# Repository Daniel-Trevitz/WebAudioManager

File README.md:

# WebAudioManager
Server program for single instance audio control via web interface

This program provides a web interface for controling an audio card.
KiCad design is found in EE folder.

This is meant to be a very simple interface with as few knobs to turn as possible

The interface is designed for mobile devices, but is functional on desktops.

http server provided by https://github.com/etr/libhttpserver
json server provided by https://github.com/nlohmann/json

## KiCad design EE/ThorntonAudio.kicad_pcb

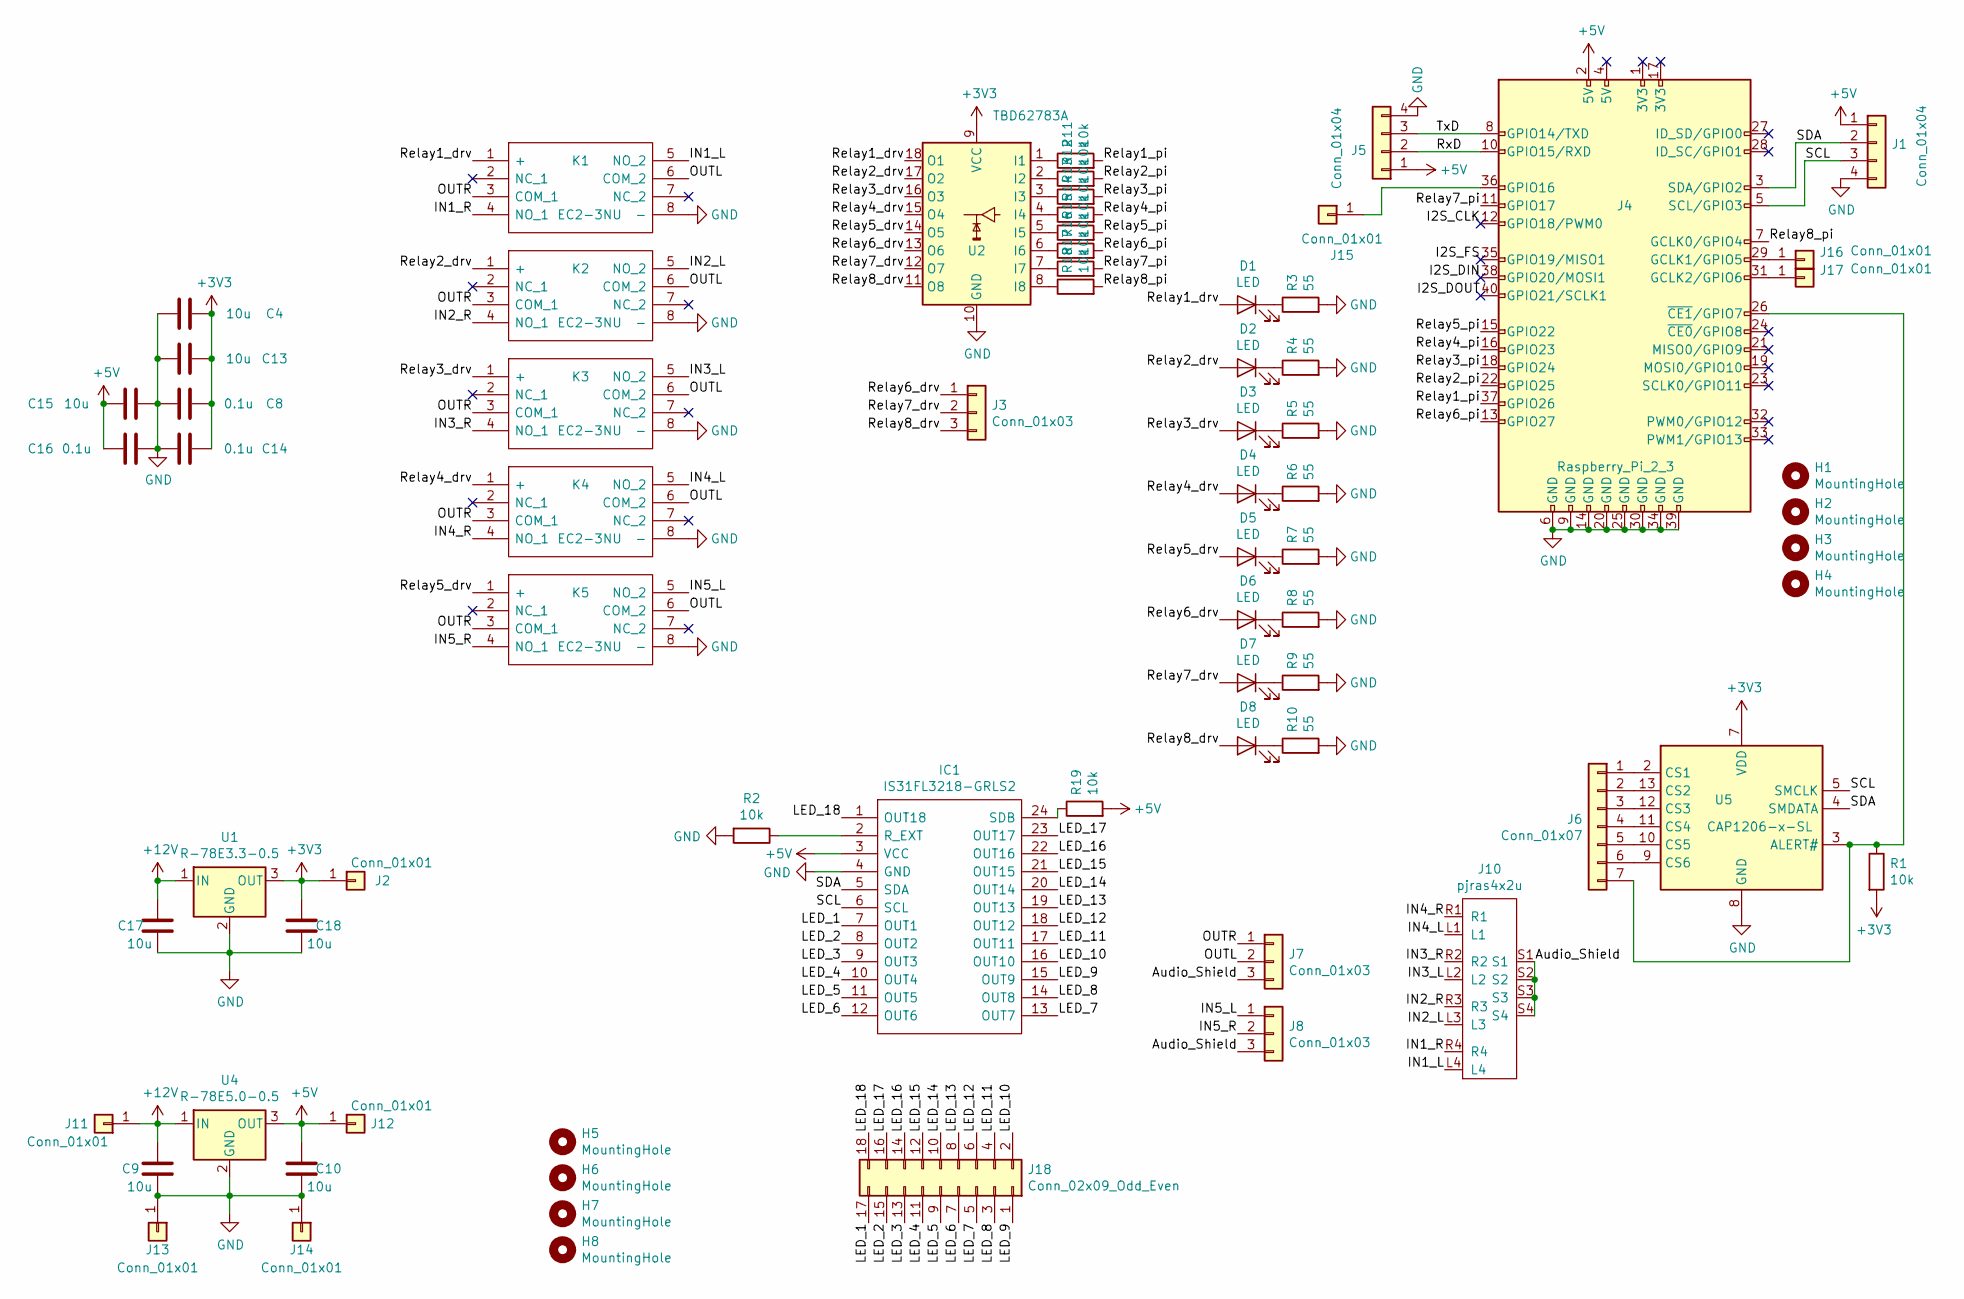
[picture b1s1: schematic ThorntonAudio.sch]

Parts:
C4, C9, C10, C13, C15, C17, C18: 10u; C_0603_1608Metric
C8, C14, C16: 0.1u; C_0603_1608Metric
D1, D2, D3, D4, D5, D6, D7, D8: LED; LED_0603_1608Metric
H1, H2, H3, H4: MountingHole; MountingHole_2.7mm
H5, H6, H7, H8: MountingHole; MountingHole_4.3mm_M4
IC1: IS31FL3218-GRLS2; SOIC127P1036X265-24N; Manufacturer_Part_Number IS31FL3218-GRLS2; Mouser Part Number 870-IS31FL3218-GRLS2
J1, J5: Conn_01x04; PinHeader_1x04_P2.54mm_Vertical
J2, J11, J12, J13, J14: Conn_01x01; SolderWirePad_1x01_Drill2.5mm
J3, J7, J8: Conn_01x03; PinHeader_1x03_P2.54mm_Vertical
J4: Raspberry_Pi_2_3; PinHeader_2x20_P2.54mm_Vertical
J6: Conn_01x07; PinHeader_1x07_P2.54mm_Vertical
J10: pjras4x2u
J15, J16, J17: Conn_01x01; PinHeader_1x01_P2.54mm_Vertical
J18: Conn_02x09_Odd_Even; PinHeader_2x09_P2.54mm_Vertical
K1, K2, K3, K4, K5: EC2-3NU; EC2-5NU; Mouser Part Number 80-EC2-3NU
R1: 10k; R_0805_2012Metric
R2: 10k; R_Axial_DIN0207_L6.3mm_D2.5mm_P2.54mm_Vertical
R3, R4, R5, R6, R7, R8, R9, R10: 55; R_0603_1608Metric
R11, R12, R13, R14, R15, R16, R17, R18, R19: 10k; R_0603_1608Metric
U1: R-78E3.3-0.5; Converter_DCDC_RECOM_R-78E-0.5_THT
U2: TBD62783A; SOP-18_7.0x12.5mm_P1.27mm
U4: R-78E5.0-0.5; Converter_DCDC_RECOM_R-78E-0.5_THT
U5: CAP1206-x-SL; SOIC-14_3.9x8.7mm_P1.27mm

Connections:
+3V3: C4.1, C8.1, C13.1, C14.1, C18.1, J2.1, R1.2, U1.3 (OUT), U2.9 (VCC), U5.7 (VDD)
+5V: C10.1, C15.2, C16.1, IC1.3 (VCC), J1.1, J4.2 (5V), J5.1, J12.1, R19.2, U4.3 (OUT)
+12V: C9.1, C17.1, J11.1, U1.1 (IN), U4.1 (IN)
/Audio_Shield: J7.3, J8.3, J10.S1, J10.S2, J10.S3, J10.S4
/I2S_CLK: J4.12 (GPIO18/PWM0)
/I2S_DIN: J4.38 (GPIO20/MOSI1)
/I2S_DOUT: J4.40 (GPIO21/SCLK1)
/I2S_FS: J4.35 (GPIO19/MISO1)
/IN1_L: J10.L4, K1.5 (NO_2)
/IN1_R: J10.R4, K1.4 (NO_1)
/IN2_L: J10.L3, K2.5 (NO_2)
/IN2_R: J10.R3, K2.4 (NO_1)
/IN3_L: J10.L2, K3.5 (NO_2)
/IN3_R: J10.R2, K3.4 (NO_1)
/IN4_L: J10.L1, K4.5 (NO_2)
/IN4_R: J10.R1, K4.4 (NO_1)
/IN5_L: J8.1, K5.5 (NO_2)
/IN5_R: J8.2, K5.4 (NO_1)
/LED_1: IC1.7 (OUT1), J18.17
/LED_2: IC1.8 (OUT2), J18.15
/LED_3: IC1.9 (OUT3), J18.13
/LED_4: IC1.10 (OUT4), J18.11
/LED_5: IC1.11 (OUT5), J18.9
/LED_6: IC1.12 (OUT6), J18.7
/LED_7: IC1.13 (OUT7), J18.5
/LED_8: IC1.14 (OUT8), J18.3
/LED_9: IC1.15 (OUT9), J18.1
/LED_10: IC1.16 (OUT10), J18.2
/LED_11: IC1.17 (OUT11), J18.4
/LED_12: IC1.18 (OUT12), J18.6
/LED_13: IC1.19 (OUT13), J18.8
/LED_14: IC1.20 (OUT14), J18.10
/LED_15: IC1.21 (OUT15), J18.12
/LED_16: IC1.22 (OUT16), J18.14
/LED_17: IC1.23 (OUT17), J18.16
/LED_18: IC1.1 (OUT18), J18.18
/OUTL: J7.2, K1.6 (COM_2), K2.6 (COM_2), K3.6 (COM_2), K4.6 (COM_2), K5.6 (COM_2)
/OUTR: J7.1, K1.3 (COM_1), K2.3 (COM_1), K3.3 (COM_1), K4.3 (COM_1), K5.3 (COM_1)
/Relay1_drv: D1.2 (A), K1.1 (+), U2.18 (O1)
/Relay1_pi: J4.37 (GPIO26), R11.2
/Relay2_drv: D2.2 (A), K2.1 (+), U2.17 (O2)
/Relay2_pi: J4.22 (GPIO25), R12.2
/Relay3_drv: D3.2 (A), K3.1 (+), U2.16 (O3)
/Relay3_pi: J4.18 (GPIO24), R13.2
/Relay4_drv: D4.2 (A), K4.1 (+), U2.15 (O4)
/Relay4_pi: J4.16 (GPIO23), R14.2
/Relay5_drv: D5.2 (A), K5.1 (+), U2.14 (O5)
/Relay5_pi: J4.15 (GPIO22), R15.2
/Relay6_drv: D6.2 (A), J3.1, U2.13 (O6)
/Relay6_pi: J4.13 (GPIO27), R16.2
/Relay7_drv: D7.2 (A), J3.2, U2.12 (O7)
/Relay7_pi: J4.11 (GPIO17), R17.2
/Relay8_drv: D8.2 (A), J3.3, U2.11 (O8)
/Relay8_pi: J4.7 (GCLK0/GPIO4), R18.2
/RxD: J4.10 (GPIO15/RXD), J5.2
/SCL: IC1.6 (SCL), J1.3, J4.5 (SCL/GPIO3), U5.5 (SMCLK)
/SDA: IC1.5 (SDA), J1.2, J4.3 (SDA/GPIO2), U5.4 (SMDATA)
/TxD: J4.8 (GPIO14/TXD), J5.3
GND: C4.2, C8.2, C9.2, C10.2, C13.2, C14.2, C15.1, C16.2, C17.2, C18.2, IC1.4 (GND), J1.4, J4.6 (GND), J4.9 (GND), J4.14 (GND), J4.20 (GND), J4.25 (GND), J4.30 (GND), J4.34 (GND), J4.39 (GND), J5.4, J13.1, J14.1, K1.8 (-), K2.8 (-), K3.8 (-), K4.8 (-), K5.8 (-), R2.2, R3.2, R4.2, R5.2, R6.2, R7.2, R8.2, R9.2, R10.2, U1.2 (GND), U2.10 (GND), U4.2 (GND), U5.8 (GND)
unnamed: D1.1 (K), R3.1
unnamed: D2.1 (K), R4.1
unnamed: D3.1 (K), R5.1
unnamed: D4.1 (K), R6.1
unnamed: D5.1 (K), R7.1
unnamed: D6.1 (K), R8.1
unnamed: D7.1 (K), R9.1
unnamed: D8.1 (K), R10.1
unnamed: IC1.2 (R_EXT), R2.1
unnamed: IC1.24 (SDB), R19.1
unnamed: J4.26 (~CE1~/GPIO7), J6.7, R1.1, U5.3 (ALERT#)
unnamed: J6.1, U5.2 (CS1)
unnamed: J6.2, U5.13 (CS2)
unnamed: J6.3, U5.12 (CS3)
unnamed: J6.4, U5.11 (CS4)
unnamed: J6.5, U5.10 (CS5)
unnamed: J6.6, U5.9 (CS6)
unnamed: J4.36 (GPIO16), J15.1
unnamed: J4.29 (GCLK1/GPIO5), J16.1
unnamed: J4.31 (GCLK2/GPIO6), J17.1
unnamed: R11.1, U2.1 (I1)
unnamed: R12.1, U2.2 (I2)
unnamed: R13.1, U2.3 (I3)
unnamed: R14.1, U2.4 (I4)
unnamed: R15.1, U2.5 (I5)
unnamed: R16.1, U2.6 (I6)
unnamed: R17.1, U2.7 (I7)
unnamed: R18.1, U2.8 (I8)

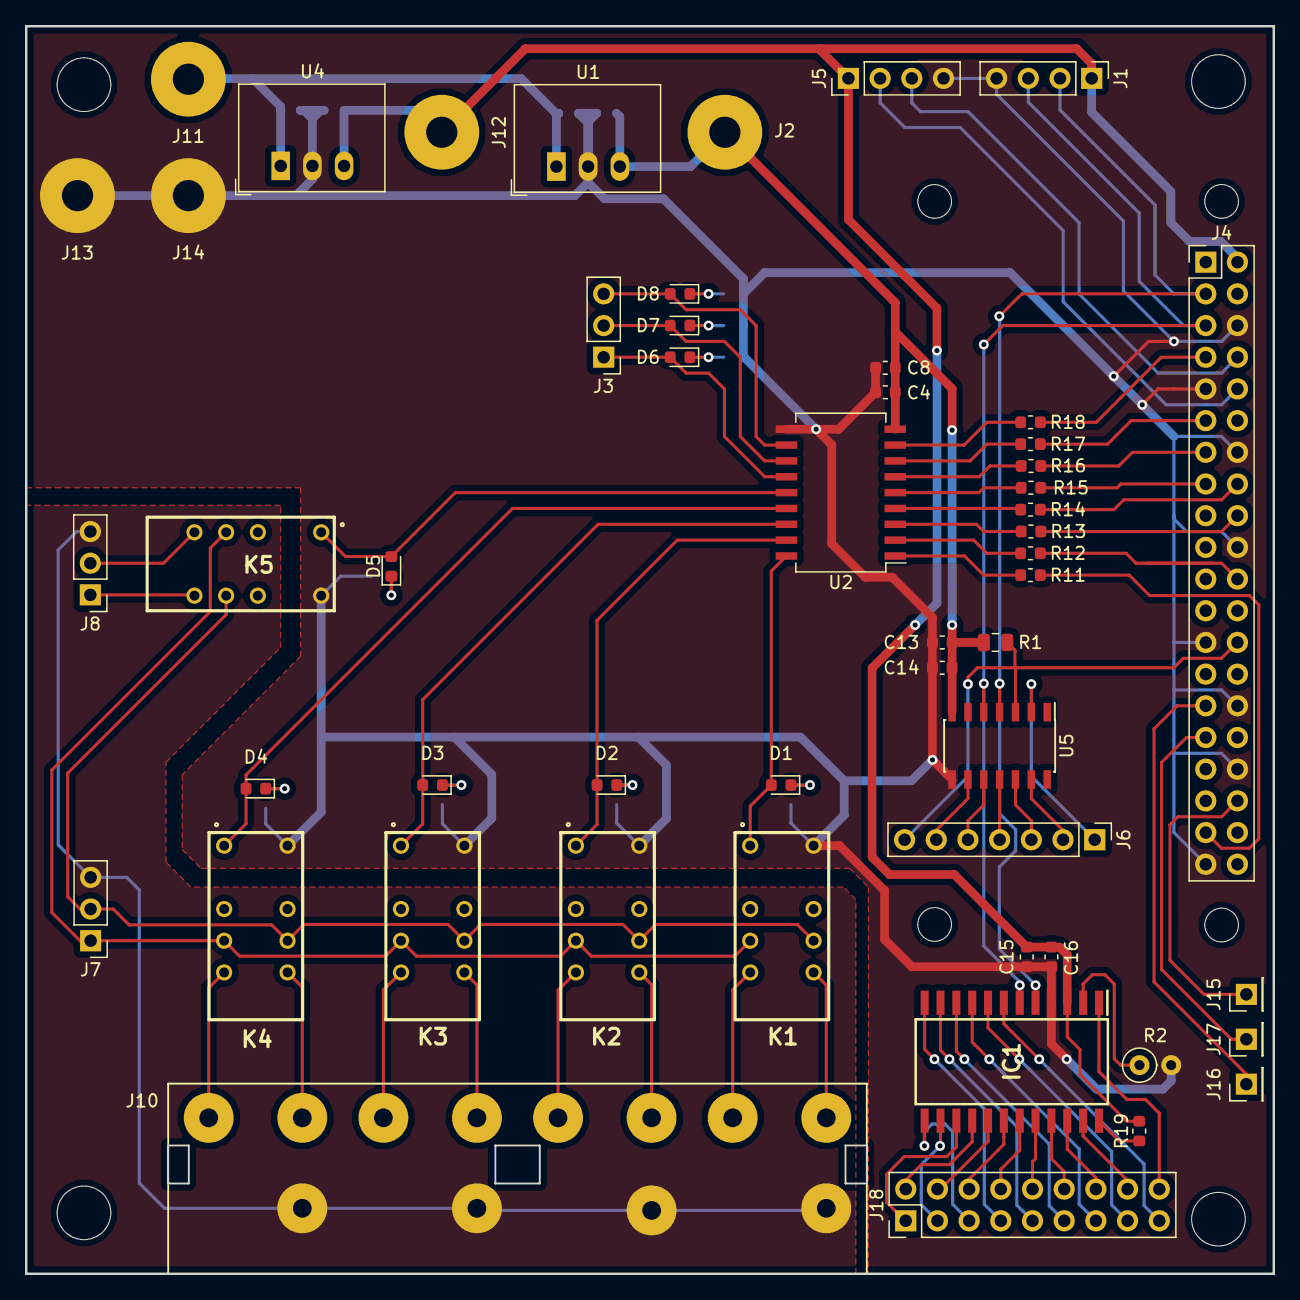
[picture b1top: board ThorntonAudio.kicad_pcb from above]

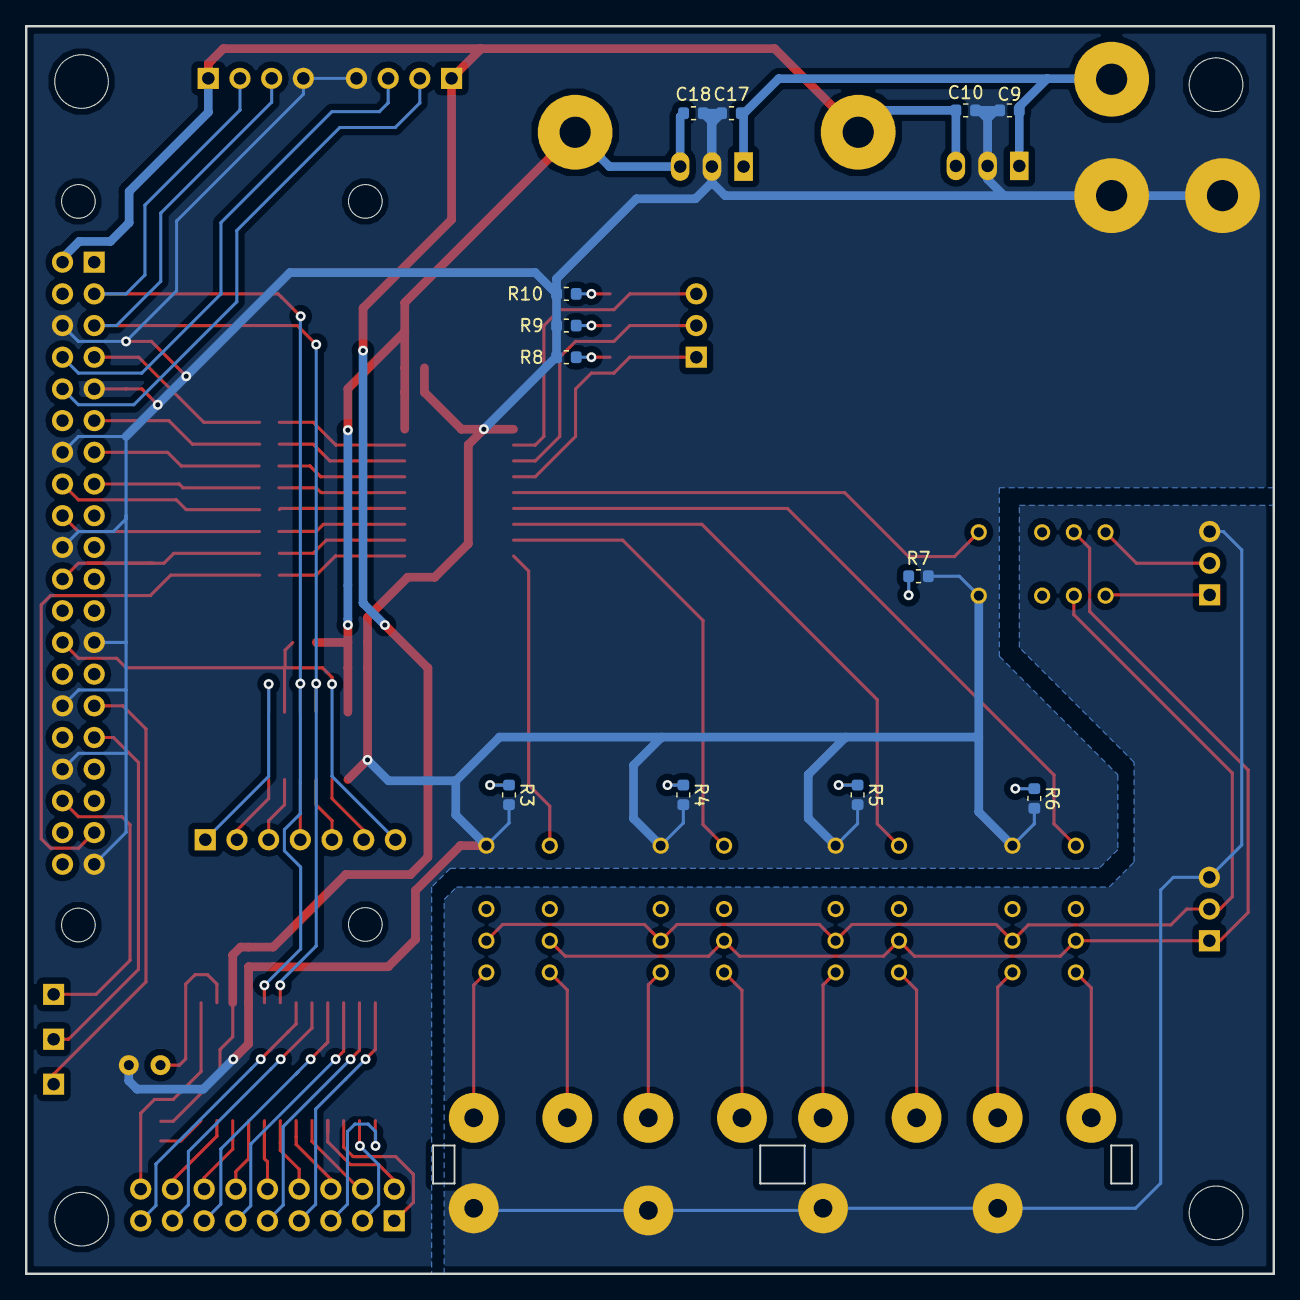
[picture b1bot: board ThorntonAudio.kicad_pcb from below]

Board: 2 copper layers, 100.0 x 100.0 mm, 72 parts (12 on the bottom side), 83 nets.

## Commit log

2019-05-17 Add starting point of git repo. Basic functionality is working
2019-05-20 Working index.html for android
2019-05-21 Working channel, radio, and CD player. cd information can be parsed via cddb. cd player is only bare bones
2019-05-21 Add the kicad design files
2019-05-21 Update the readme
2019-05-21 Add .gitignore and remove user file
2019-05-21 Remove index_html class - never used it
2019-05-21 Add some attribution
2019-05-21 Remove unused status class
2019-05-22 Move all the files around to make a clean structure
2019-05-27 Complete the CD interface. Add the CDDB access.
2019-05-29 Add mute function
2019-05-29 Begin work on the CD Ripping
2019-05-29 Add some missing files. Implement recursive mkdir and a simple playlist cache
2019-11-20 commit library.html
2019-12-02 Many changes since last commit. Essentially a working system now
2020-08-16 A whole lot of changes and it's been so long I forget what why and where and am to lazy to look it up and no one cares so time to barf over the commit history
